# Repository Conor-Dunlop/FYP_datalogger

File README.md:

# ENEL400 datalogger

render of the datalogger with power board (yes i know it need routed)

this project has 2 main dirs
## hardware
this is where all the schmatics and PCBs live
within here you have the 
- `WB_based_board/datalogger` depecated one of lui projects that uses an stm32 with wireless built in
- `g4_based_board` has the schmatics and PCB for the datalogger
- `libs` for custom parts that wernt in kicad
- `lorawan_board/LoRaWAN_Board` never used dont look at this
- `power_board` as a power board that support 1 cell lipo and an external dc voltage
- `power_supply_module` i have forgotten more then likely the same as power_board

## software
this is where all the software for the project lives
- `conor code` this is where some depecated stm32cube projects live
- `ESP32_comms` this is where a basic code for the ESP32 lives
  - this code allow for any data spat out form the data logger to be sent off through an https request to some server, (i would suggest using the server in `emulator`)
- `Heltec ESP32 code` this is where the code live for a basic lorawan setup live 
- `joshM code/OLD_BOARD_SOFTWARE_UART_COMMS` this is josh Ms "Fork" of the `OLD_BOARD_SOFTWARE_UART_COMMS` code
- `New_G4_Software` this has basic code for the most recent PCB use the `NEW_G4_software.ioc` for creating any new projects you may need
- `OLD_BOARD_SOFTWARE_UART_COMMS` this is code that send a count a button count, a state that can be changed with buttons and an ADC value that gets sent over comms interface using UART, to be used in tandom with the `ESP32_comms` code
- `WB_software` depecated uses an stm32 that has wireless support
- `data_formats` holds the schema for the database on asure
- `dataloggerAPI` asure cloud server that handles all the HTTP requests and database lookups
- `emulator` emulates the datalogger so you can test server code with out a physical data logger 
- `g4_software` depecated fpr use on the original board

for any ESP32 code it is suggested to connect to a moblie hot spot as the uc wireless doesnt like them.
the software is a mess because some people dont know how to branch code

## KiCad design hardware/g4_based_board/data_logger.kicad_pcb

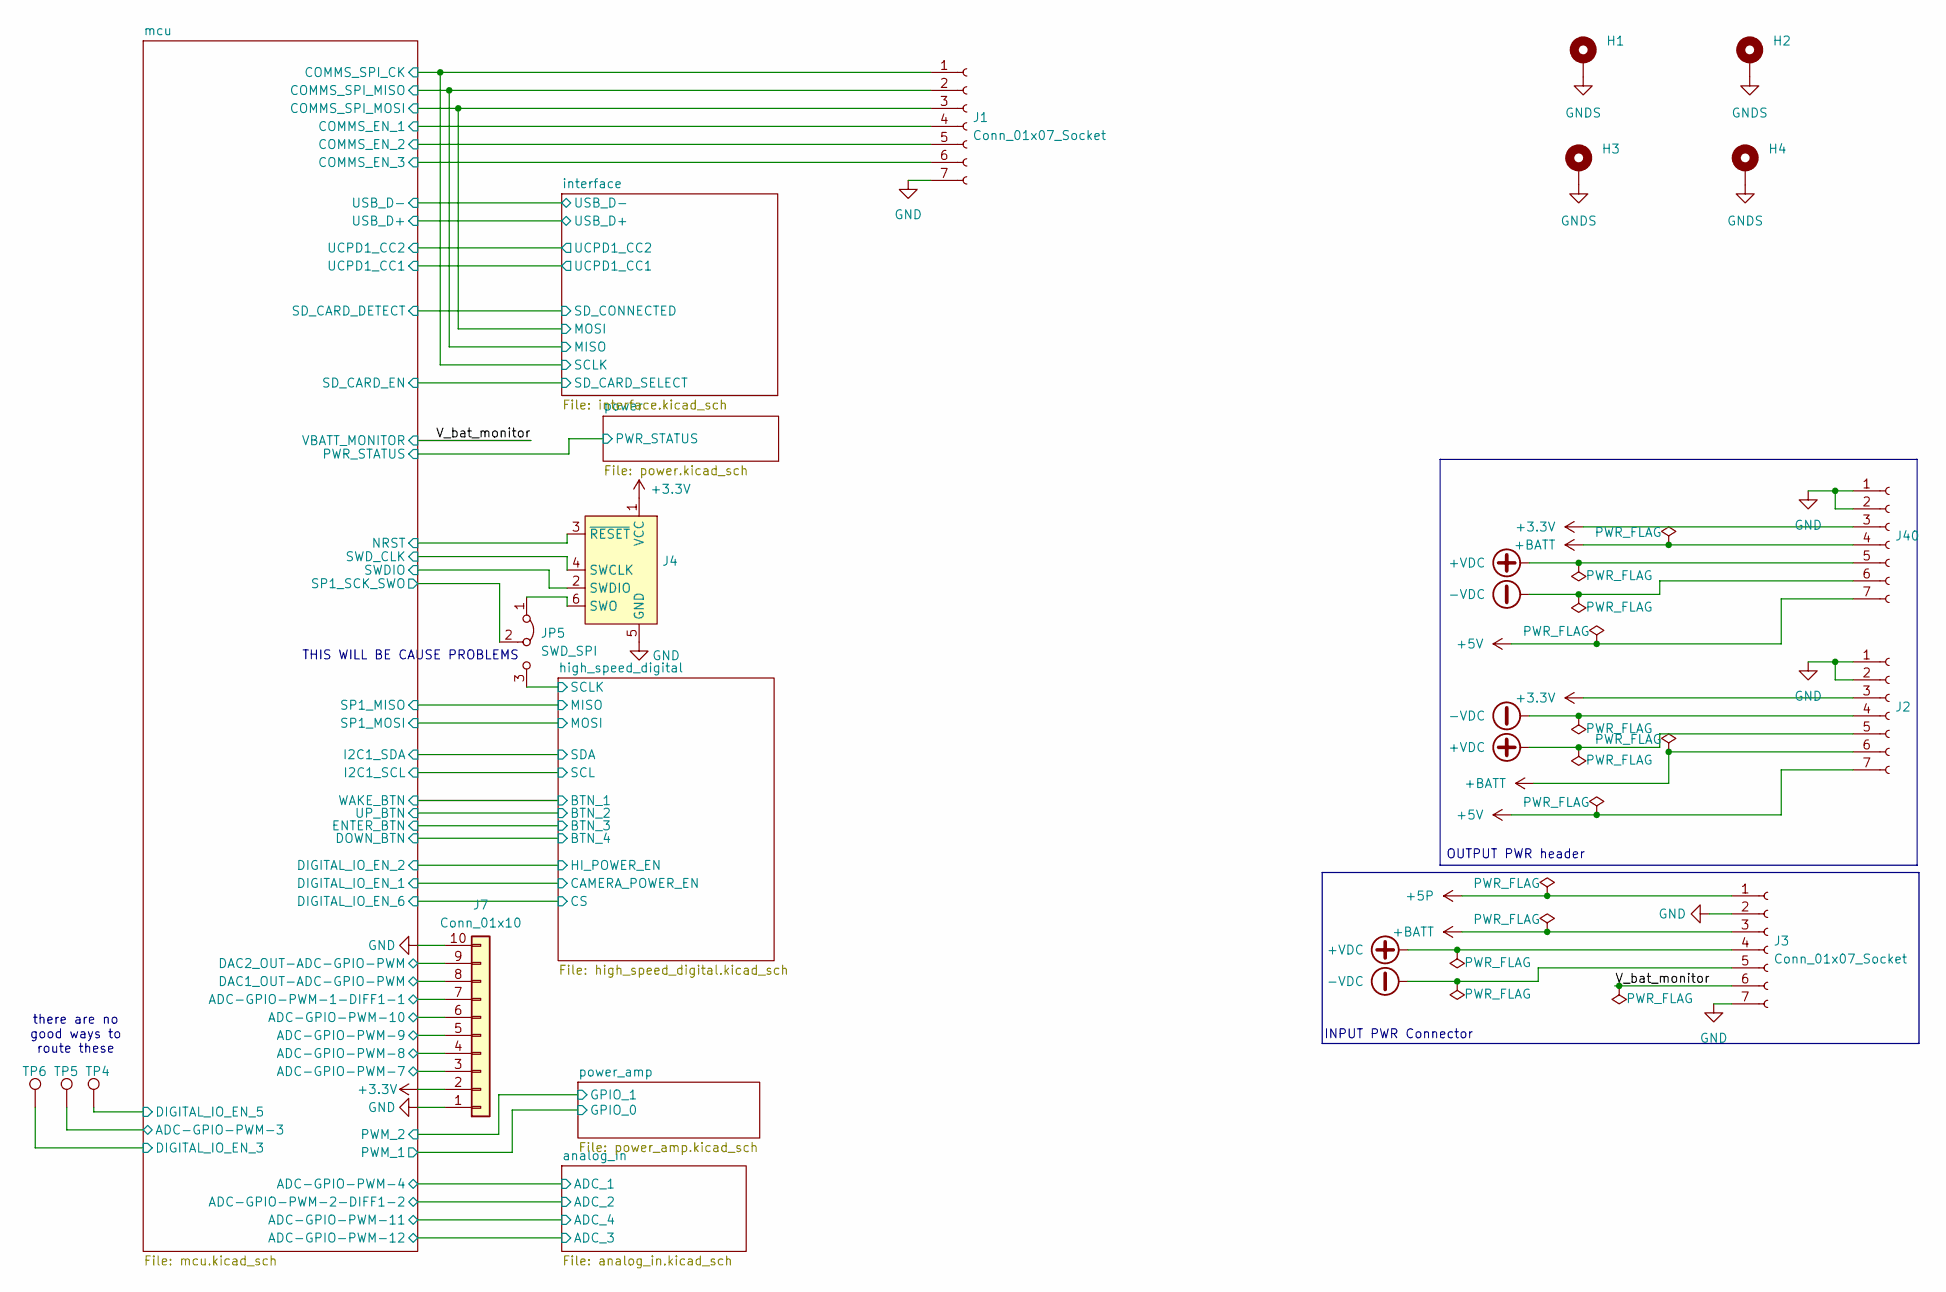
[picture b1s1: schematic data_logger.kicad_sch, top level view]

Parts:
H1, H2, H3, H4: MountingHole_Pad; MountingHole_3.2mm_M3_DIN965_Pad_TopOnly
J1, J2, J3, J40: Conn_01x07_Socket; PinHeader_1x07_P2.54mm_Vertical
J4: Conn_ARM_SWD_TagConnect_TC2030-NL; Tag-Connect_TC2030-IDC-FP_2x03_P1.27mm_Vertical
J7: Conn_01x10; PinHeader_1x10_P2.54mm_Vertical
JP5: SWD_SPI; SolderJumper-3_P1.3mm_Bridged2Bar12_RoundedPad1.0x1.5mm
TP4, TP5, TP6: TestPoint; TestPoint_Pad_2.0x2.0mm

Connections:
+3.3V: J2.3, J4.1 (VCC), J7.2, J40.3; also elsewhere on the board
+5P: J3.1; also elsewhere on the board
+5V: J2.7, J40.7; also elsewhere on the board
+BATT: J2.6, J3.3, J40.4; also elsewhere on the board
+VDC: J2.5, J3.4, J40.5
-VDC: J2.4, J3.5, J40.6
/V_bat_monitor: J3.6; also elsewhere on the board
/high_speed_digital/SCLK: JP5.3 (B); also elsewhere on the board
/interface/MISO: J1.2; also elsewhere on the board
/interface/MOSI: J1.3; also elsewhere on the board
/interface/SCLK: J1.1; also elsewhere on the board
/mcu/ADC-GPIO-PWM-1-DIFF1-1: J7.7; also elsewhere on the board
/mcu/ADC-GPIO-PWM-3: TP5.1; also elsewhere on the board
/mcu/ADC-GPIO-PWM-7: J7.3; also elsewhere on the board
/mcu/ADC-GPIO-PWM-8: J7.4; also elsewhere on the board
/mcu/ADC-GPIO-PWM-9: J7.5; also elsewhere on the board
/mcu/ADC-GPIO-PWM-10: J7.6; also elsewhere on the board
/mcu/COMMS_EN_1: J1.4; also elsewhere on the board
/mcu/COMMS_EN_2: J1.5; also elsewhere on the board
/mcu/COMMS_EN_3: J1.6; also elsewhere on the board
/mcu/DAC1_OUT-ADC-GPIO-PWM: J7.8; also elsewhere on the board
/mcu/DAC2_OUT-ADC-GPIO-PWM: J7.9; also elsewhere on the board
/mcu/DIGITAL_IO_EN_3: TP6.1; also elsewhere on the board
/mcu/DIGITAL_IO_EN_5: TP4.1; also elsewhere on the board
/mcu/NRST: J4.3 (~RESET); also elsewhere on the board
/mcu/SP1_SCK_SWO: JP5.2 (C); also elsewhere on the board
/mcu/SWDIO: J4.2 (SWDIO); also elsewhere on the board
/mcu/SWD_CLK: J4.4 (SWCLK); also elsewhere on the board
GND: J1.7, J2.1, J2.2, J3.2, J3.7, J4.5 (GND), J7.1, J7.10, J40.1, J40.2; also elsewhere on the board
GNDS: H1.1, H2.1, H3.1, H4.1; also elsewhere on the board
unnamed: J4.6 (SWO), JP5.1 (A)

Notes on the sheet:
THIS WILL BE CAUSE PROBLEMS
INPUT PWR Connector
there are no good ways to route these
OUTPUT PWR header

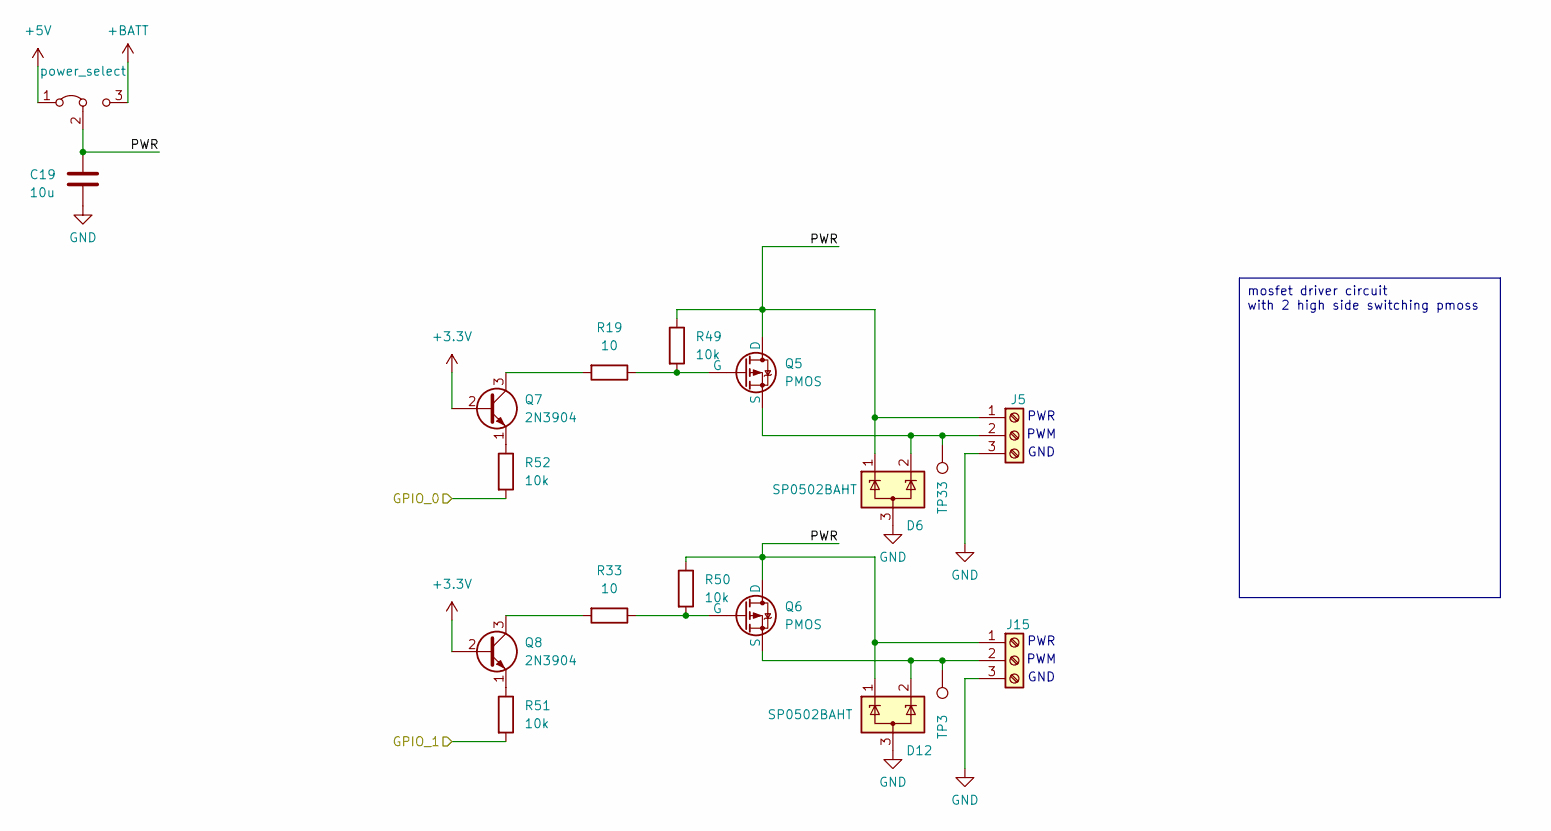
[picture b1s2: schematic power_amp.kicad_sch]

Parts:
C19: 10u; C_0603_1608Metric_Pad1.08x0.95mm_HandSolder
D6, D12: SP0502BAHT; SOT-23
J5, J15: Screw_Terminal_01x03; TerminalBlock_Altech_AK300-3_P5.00mm
JP6: power_select; PinHeader_1x03_P2.54mm_Vertical
Q5, Q6: PMOS; TO-247-3_Vertical
Q7, Q8: 2N3904; TO-92_Inline
R19, R33: 10; R_0603_1608Metric_Pad0.98x0.95mm_HandSolder
R49, R50, R51, R52: 10k; R_0603_1608Metric_Pad0.98x0.95mm_HandSolder
TP3, TP33: GPIO_INPUT_PRE; TestPoint_Keystone_5019_Minature

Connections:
+3.3V: Q7.2 (B), Q8.2 (B); also elsewhere on the board
+5V: JP6.1 (A); also elsewhere on the board
+BATT: JP6.3 (B); also elsewhere on the board
/mcu/PWM_1: R52.2; also elsewhere on the board
/mcu/PWM_2: R51.2; also elsewhere on the board
/power_amp/PWR: C19.1, D6.1 (K), D12.1 (K), J5.1, J15.1, JP6.2 (C), Q5.1 (D), Q6.1 (D), R49.1, R50.1
GND: C19.2, D6.3 (A), D12.3 (A), J5.3, J15.3; also elsewhere on the board
unnamed: D6.2 (K), J5.2, Q5.3 (S), TP33.1
unnamed: D12.2 (K), J15.2, Q6.3 (S), TP3.1
unnamed: Q5.2 (G), R19.1, R49.2
unnamed: Q6.2 (G), R33.1, R50.2
unnamed: Q7.3 (C), R19.2
unnamed: Q7.1 (E), R52.1
unnamed: Q8.3 (C), R33.2
unnamed: Q8.1 (E), R51.1

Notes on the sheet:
mosfet driver circuit with 2 high side switching pmoss
GND
PWR
PWM

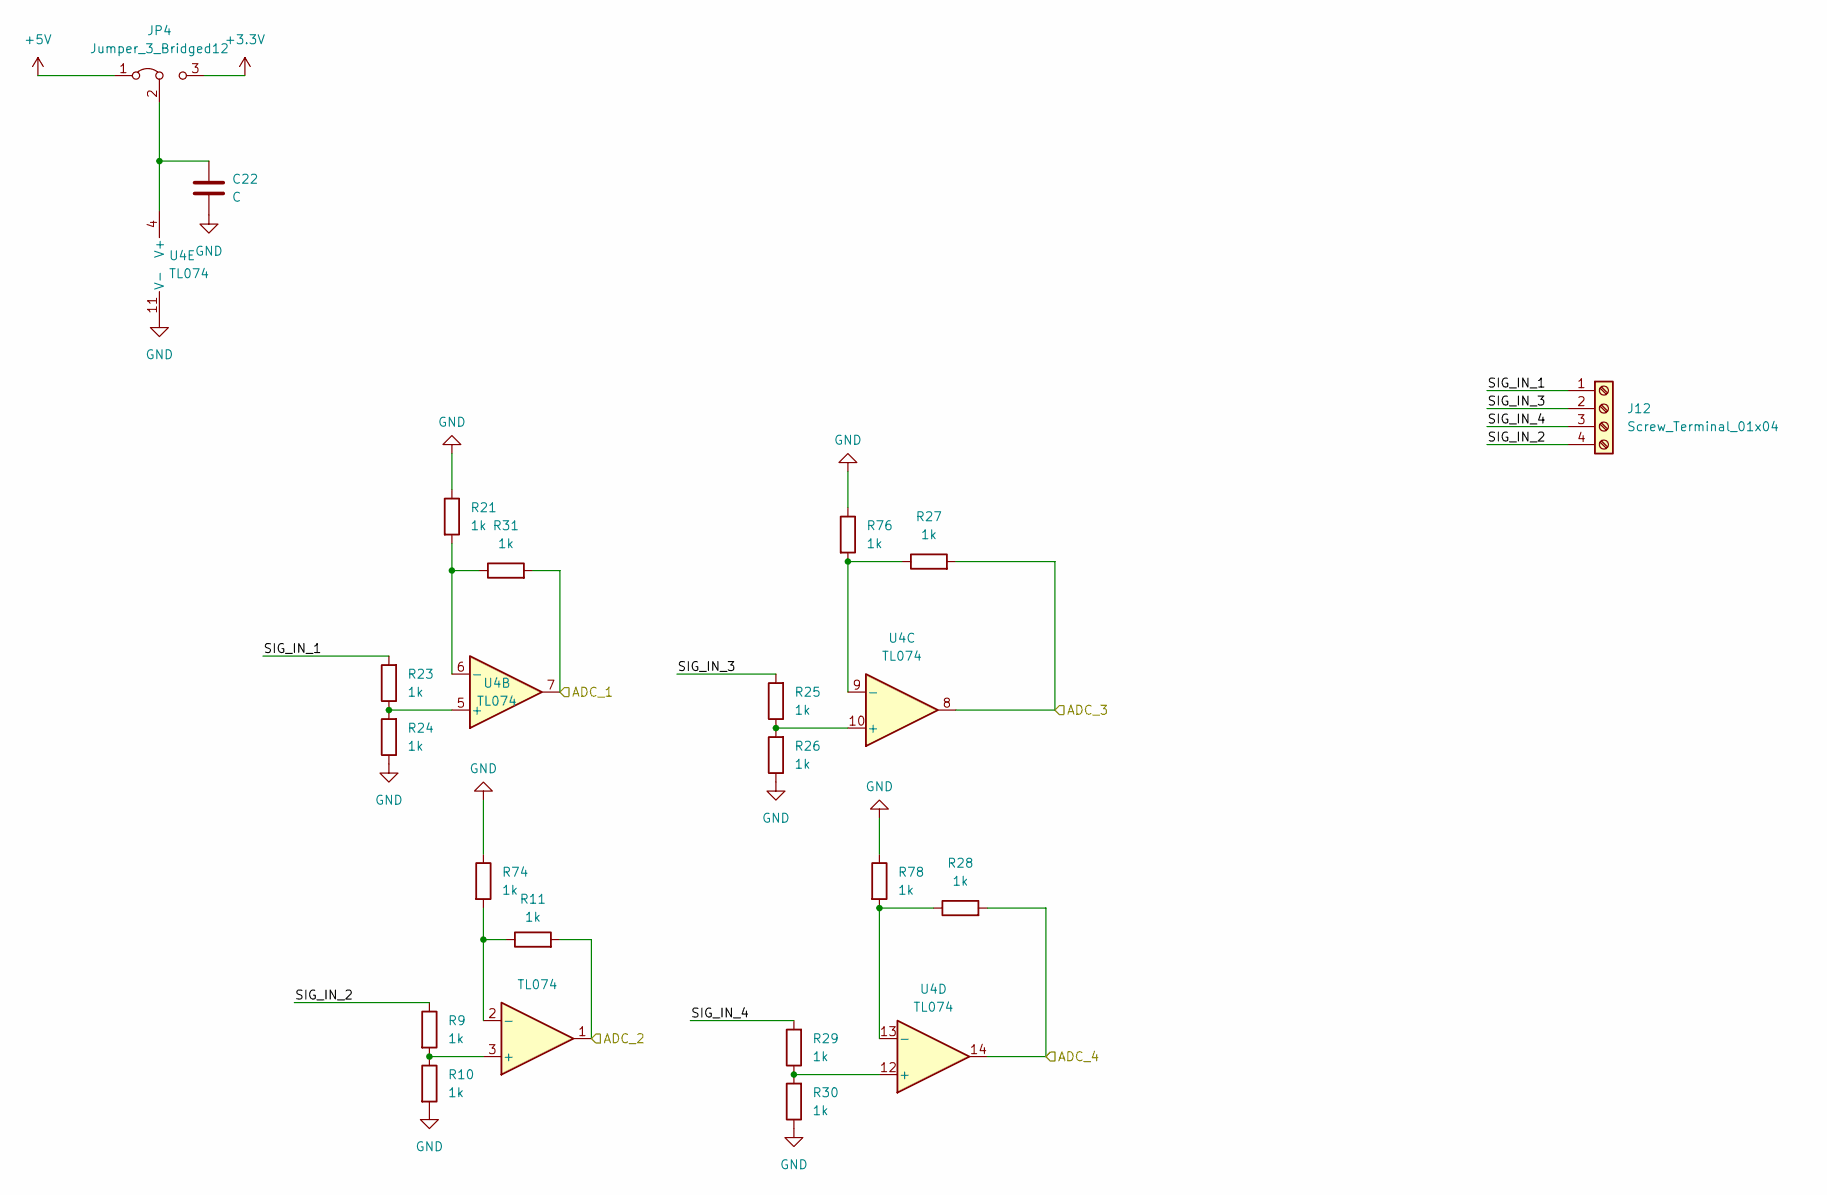
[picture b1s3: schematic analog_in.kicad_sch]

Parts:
C22: C; C_0603_1608Metric_Pad1.08x0.95mm_HandSolder
J12: Screw_Terminal_01x04; TerminalBlock_Altech_AK300-4_P5.00mm
JP4: Jumper_3_Bridged12; PinHeader_1x03_P2.54mm_Vertical
R9, R10, R11, R21, R23, R24, R25, R26, R27, R28, R29, R30, R31, R74, R76, R78: 1k; R_0603_1608Metric_Pad0.98x0.95mm_HandSolder
U4: TL074; SOIC-14_3.9x8.7mm_P1.27mm

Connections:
+3.3V: JP4.3 (B); also elsewhere on the board
+5V: JP4.1 (A); also elsewhere on the board
/analog_in/ADC_1: R31.2, U4.7; also elsewhere on the board
/analog_in/ADC_2: R11.2, U4.1; also elsewhere on the board
/analog_in/ADC_3: R27.2, U4.8; also elsewhere on the board
/analog_in/ADC_4: R28.2, U4.14; also elsewhere on the board
/analog_in/SIG_IN_2: J12.4, R9.1
/analog_in/SIG_IN_3: J12.2, R25.2
GND: C22.2, R10.2, R21.1, R24.1, R26.1, R30.1, R74.1, R76.1, R78.1, U4.11 (V-); also elsewhere on the board
unnamed: C22.1, JP4.2 (C), U4.4 (V+)
unnamed: R9.2, R10.1, U4.3 (+)
unnamed: R11.1, R74.2, U4.2 (-)
unnamed: R23.1, R24.2, U4.5 (+)
unnamed: R21.2, R31.1, U4.6 (-)
unnamed: R25.1, R26.2, U4.10 (+)
unnamed: R27.1, R76.2, U4.9 (-)
unnamed: R29.1, R30.2, U4.12 (+)
unnamed: R28.1, R78.2, U4.13 (-)

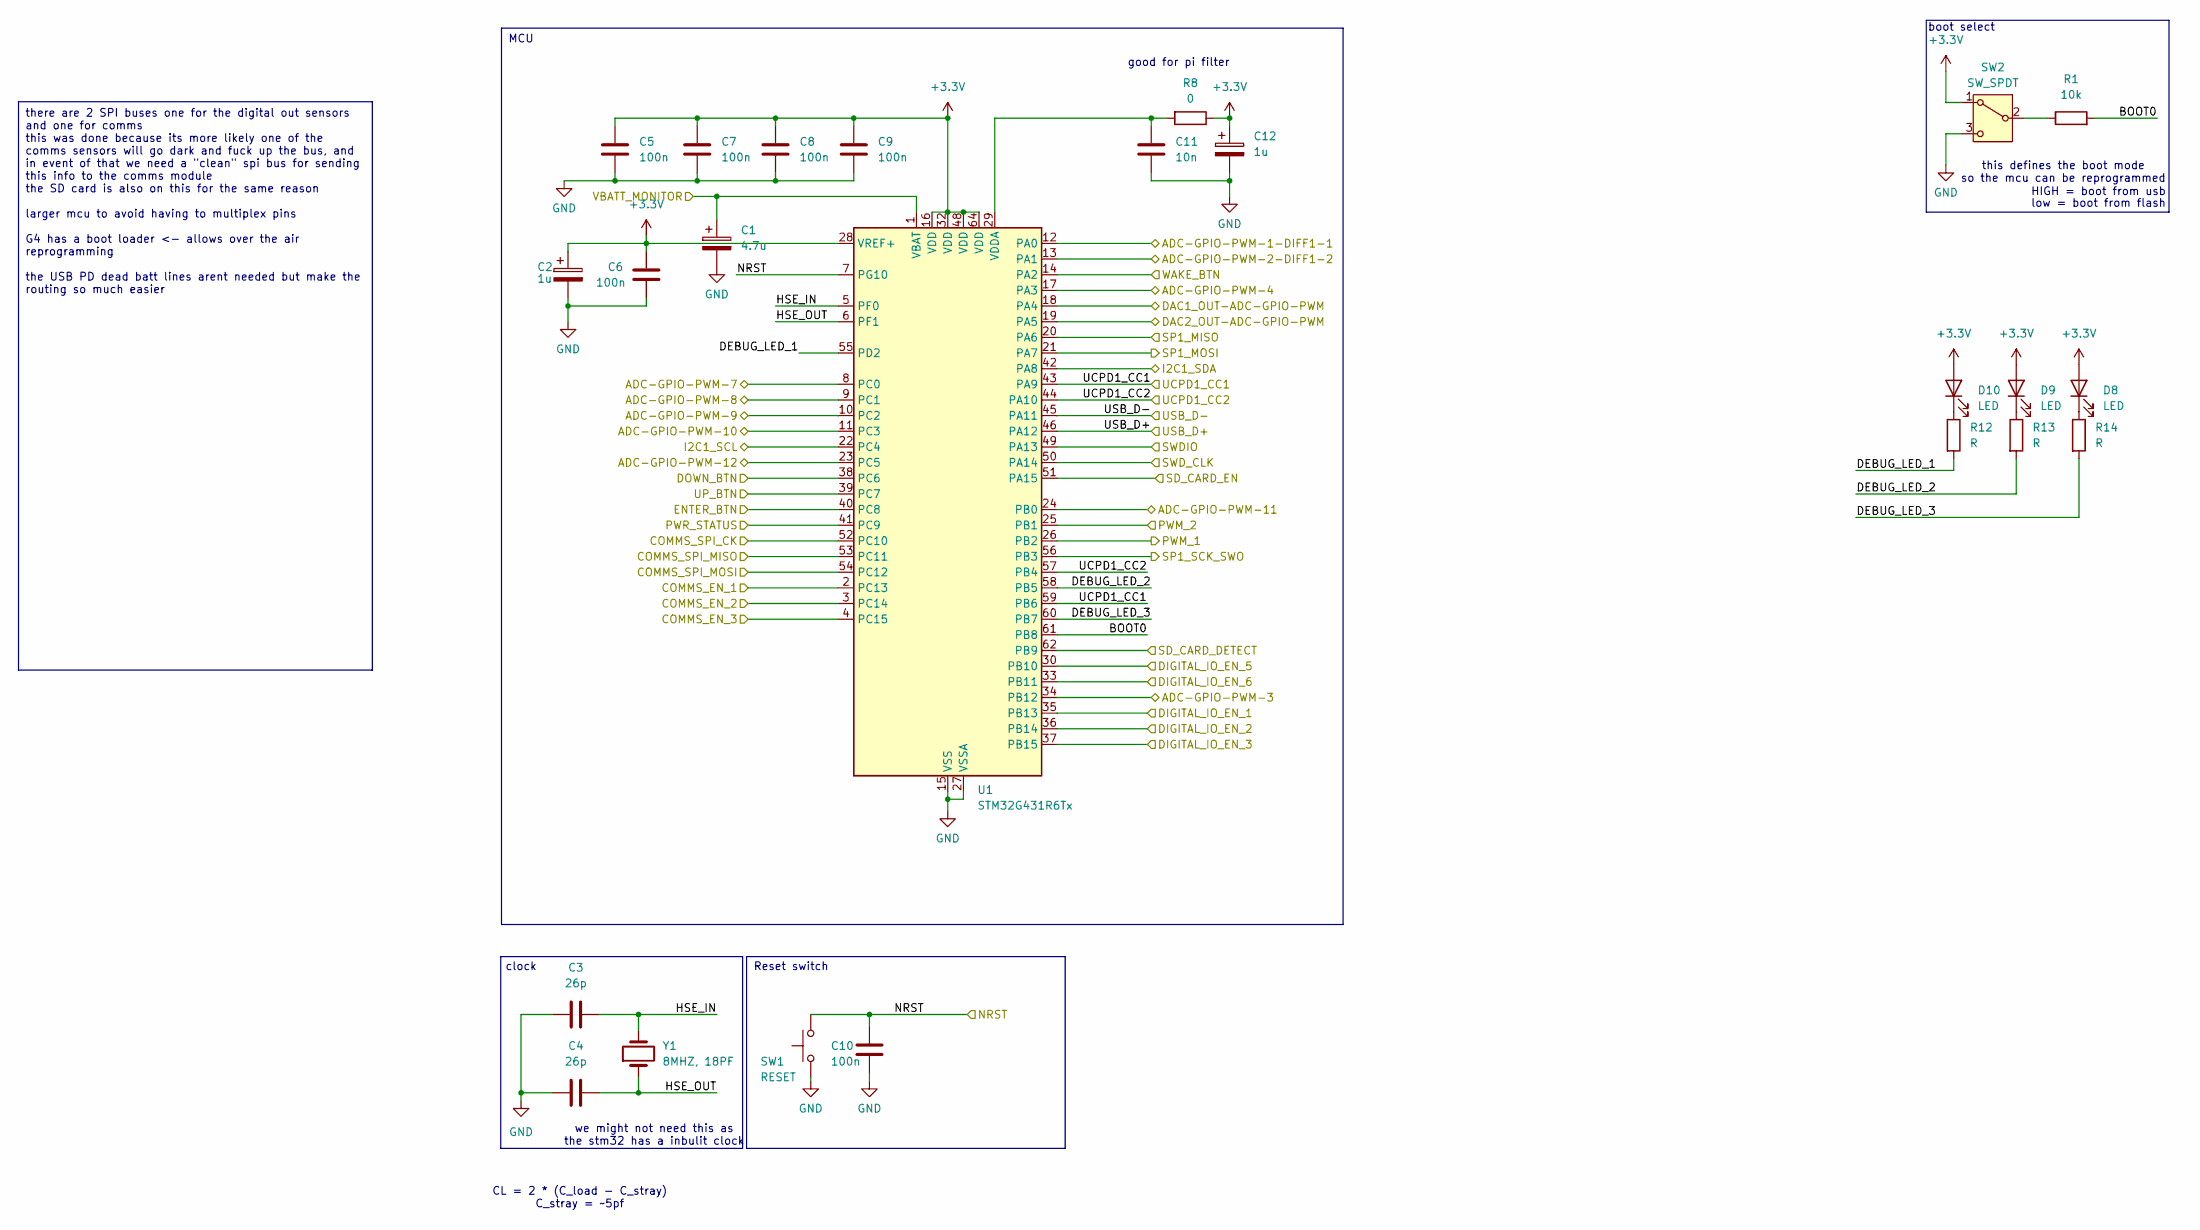
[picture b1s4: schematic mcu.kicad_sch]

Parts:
C1: 4.7u; C_0603_1608Metric_Pad1.08x0.95mm_HandSolder
C2, C12: 1u; C_0603_1608Metric_Pad1.08x0.95mm_HandSolder
C3, C4: 26p; C_0603_1608Metric_Pad1.08x0.95mm_HandSolder
C5, C6, C7, C8, C9, C10: 100n; C_0603_1608Metric_Pad1.08x0.95mm_HandSolder
C11: 10n; C_0603_1608Metric_Pad1.08x0.95mm_HandSolder
D8, D9, D10: LED; LED_0603_1608Metric
R1: 10k; R_0603_1608Metric_Pad0.98x0.95mm_HandSolder
R8: 0; R_0603_1608Metric
R12, R13, R14: R; R_0603_1608Metric_Pad0.98x0.95mm_HandSolder
SW1: RESET; SW_Push_SPST_NO_Alps_SKRK
SW2: SW_SPDT; SW_Slide_SPDT_Angled_CK_OS102011MA1Q
U1: STM32G431R6Tx; LQFP-64_10x10mm_P0.5mm
Y1: 8MHZ, 18PF; Crystal_SMD_TXC_7A-2Pin_5x3.2mm

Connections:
+3.3V: C2.1, C5.1, C6.1, C7.1, C8.1, C9.1, C12.1, D8.2 (A), D9.2 (A), D10.2 (A), R8.1, SW2.1 (A), U1.16 (VDD), U1.28 (VREF+), U1.32 (VDD), U1.48 (VDD), U1.64 (VDD); also elsewhere on the board
/V_bat_monitor: C1.1, U1.1 (VBAT); also elsewhere on the board
/analog_in/ADC_1: U1.17 (PA3); also elsewhere on the board
/analog_in/ADC_2: U1.13 (PA1); also elsewhere on the board
/analog_in/ADC_3: U1.23 (PC5); also elsewhere on the board
/analog_in/ADC_4: U1.24 (PB0); also elsewhere on the board
/high_speed_digital/BTN_1: U1.14 (PA2); also elsewhere on the board
/high_speed_digital/BTN_2: U1.39 (PC7); also elsewhere on the board
/high_speed_digital/BTN_3: U1.40 (PC8); also elsewhere on the board
/high_speed_digital/BTN_4: U1.38 (PC6); also elsewhere on the board
/high_speed_digital/CAMERA_POWER_EN: U1.35 (PB13); also elsewhere on the board
/high_speed_digital/CS: U1.33 (PB11); also elsewhere on the board
/high_speed_digital/HI_POWER_EN: U1.36 (PB14); also elsewhere on the board
/high_speed_digital/MISO: U1.20 (PA6); also elsewhere on the board
/high_speed_digital/MOSI: U1.21 (PA7); also elsewhere on the board
/interface/MISO: U1.53 (PC11); also elsewhere on the board
/interface/MOSI: U1.54 (PC12); also elsewhere on the board
/interface/SCLK: U1.52 (PC10); also elsewhere on the board
/interface/SD_CARD_SELECT: U1.51 (PA15); also elsewhere on the board
/interface/SD_CONNECTED: U1.62 (PB9); also elsewhere on the board
/mcu/ADC-GPIO-PWM-1-DIFF1-1: U1.12 (PA0); also elsewhere on the board
/mcu/ADC-GPIO-PWM-3: U1.34 (PB12); also elsewhere on the board
/mcu/ADC-GPIO-PWM-7: U1.8 (PC0); also elsewhere on the board
/mcu/ADC-GPIO-PWM-8: U1.9 (PC1); also elsewhere on the board
/mcu/ADC-GPIO-PWM-9: U1.10 (PC2); also elsewhere on the board
/mcu/ADC-GPIO-PWM-10: U1.11 (PC3); also elsewhere on the board
/mcu/BOOT0: R1.2, U1.61 (PB8)
/mcu/COMMS_EN_1: U1.2 (PC13); also elsewhere on the board
/mcu/COMMS_EN_2: U1.3 (PC14); also elsewhere on the board
/mcu/COMMS_EN_3: U1.4 (PC15); also elsewhere on the board
/mcu/DAC1_OUT-ADC-GPIO-PWM: U1.18 (PA4); also elsewhere on the board
/mcu/DAC2_OUT-ADC-GPIO-PWM: U1.19 (PA5); also elsewhere on the board
/mcu/DEBUG_LED_1: R12.2, U1.55 (PD2)
/mcu/DEBUG_LED_2: R13.2, U1.58 (PB5)
/mcu/DEBUG_LED_3: R14.2, U1.60 (PB7)
/mcu/DIGITAL_IO_EN_3: U1.37 (PB15); also elsewhere on the board
/mcu/DIGITAL_IO_EN_5: U1.30 (PB10); also elsewhere on the board
/mcu/HSE_IN: C3.1, U1.5 (PF0), Y1.2
/mcu/HSE_OUT: C4.1, U1.6 (PF1), Y1.1
/mcu/NRST: C10.2, SW1.2, U1.7 (PG10); also elsewhere on the board
/mcu/PWM_1: U1.26 (PB2); also elsewhere on the board
/mcu/PWM_2: U1.25 (PB1); also elsewhere on the board
/mcu/PWR_STATUS: U1.41 (PC9); also elsewhere on the board
/mcu/SP1_SCK_SWO: U1.56 (PB3); also elsewhere on the board
/mcu/SWDIO: U1.49 (PA13); also elsewhere on the board
/mcu/SWD_CLK: U1.50 (PA14); also elsewhere on the board
/mcu/UCPD1_CC1: U1.43 (PA9), U1.59 (PB6); also elsewhere on the board
/mcu/UCPD1_CC2: U1.44 (PA10), U1.57 (PB4); also elsewhere on the board
/mcu/USB_D+: U1.46 (PA12); also elsewhere on the board
/mcu/USB_D-: U1.45 (PA11); also elsewhere on the board
GND: C1.2, C2.2, C3.2, C4.2, C5.2, C6.2, C7.2, C8.2, C9.2, C10.1, C11.2, C12.2, SW1.1, SW2.3 (C), U1.15 (VSS), U1.27 (VSSA), U1.31 (VSS), U1.47 (VSS), U1.63 (VSS); also elsewhere on the board
unnamed: D8.1 (K), R14.1
unnamed: D9.1 (K), R13.1
unnamed: D10.1 (K), R12.1
unnamed: R1.1, SW2.2 (B)
unnamed: C11.1, R8.2, U1.29 (VDDA)

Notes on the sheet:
there are 2 SPI buses one for the digital out sensors and one for comms this was done because its more likely one of the comms sensors will go dark and fuck up the bus, and in event of that we need a "clean" spi bus for sending this info to the comms module the SD card is also on this for the same 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
good for pi filter
boot select
clock
MCU
Reset switch
HIGH = boot from usb
CL = 2 * (C_load - C_stray) C_stray = ~5pf
this defines the boot mode so the mcu can be reprogrammed
low = boot from flash
we might not need this as the stm32 has a inbulit clock

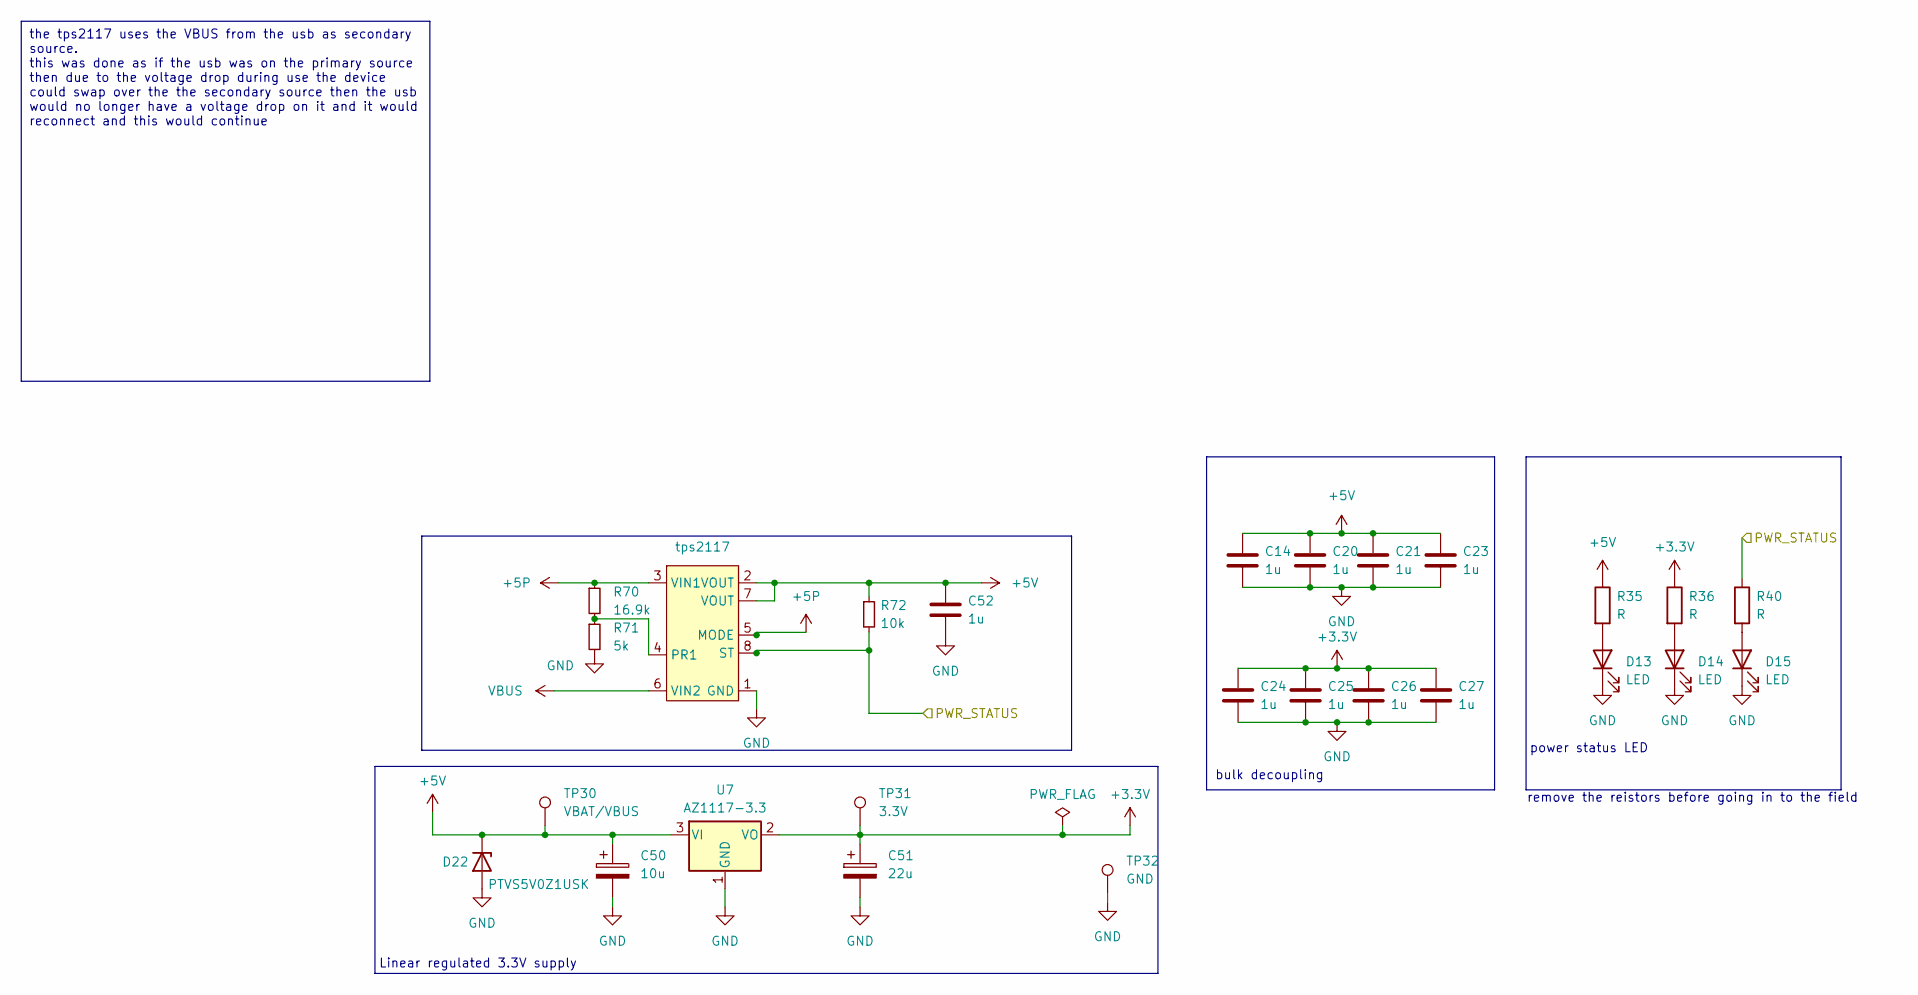
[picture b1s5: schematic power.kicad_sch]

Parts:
C14, C20, C21, C23, C24, C25, C26, C27, C52: 1u; C_0603_1608Metric_Pad1.08x0.95mm_HandSolder
C50: 10u; C_0603_1608Metric_Pad1.08x0.95mm_HandSolder
C51: 22u; C_0603_1608Metric_Pad1.08x0.95mm_HandSolder
D13, D14, D15: LED; LED_0603_1608Metric
D22: PTVS5V0Z1USK; Nexperia_DSN1608-2_1.6x0.8mm
R35, R36, R40: R; R_0603_1608Metric_Pad0.98x0.95mm_HandSolder
R70: 16.9k; R_0603_1608Metric_Pad0.98x0.95mm_HandSolder
R71: 5k; R_0603_1608Metric_Pad0.98x0.95mm_HandSolder
R72: 10k; R_0603_1608Metric_Pad0.98x0.95mm_HandSolder
TP30: VBAT/VBUS; TestPoint_Pad_D1.5mm
TP31: 3.3V; TestPoint_Pad_D1.5mm
TP32: GND; TestPoint_Pad_D1.5mm
U6: tps2117; SOT-583-8
U7: AZ1117-3.3; SOT-223

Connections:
+3.3V: C24.1, C25.1, C26.1, C27.1, C51.1, R36.1, TP31.1, U7.2 (VO); also elsewhere on the board
+5P: R70.1, U6.3 (VIN1), U6.5 (MODE); also elsewhere on the board
+5V: C14.1, C20.1, C21.1, C23.1, C50.1, C52.1, D22.1 (K), R35.1, R72.1, TP30.1, U6.2 (VOUT), U6.7 (VOUT), U7.3 (VI); also elsewhere on the board
/mcu/PWR_STATUS: R40.1, R72.2, U6.8 (ST); also elsewhere on the board
GND: C14.2, C20.2, C21.2, C23.2, C24.2, C25.2, C26.2, C27.2, C50.2, C51.2, C52.2, D13.1 (K), D14.1 (K), D15.1 (K), D22.2 (A), R71.2, TP32.1, U6.1 (GND), U7.1 (GND); also elsewhere on the board
unnamed: D13.2 (A), R35.2
unnamed: D14.2 (A), R36.2
unnamed: D15.2 (A), R40.2
unnamed: R70.2, R71.1, U6.4 (PR1)
VBUS: U6.6 (VIN2); also elsewhere on the board

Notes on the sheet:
the tps2117 uses the VBUS from the usb as secondary source. this was done as if the usb was on the primary source then due to the voltage drop during use the device could swap over the the secondary source then the usb would no longer have a voltage drop on it and it would reconnect and this would 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
bulk decoupling
remove the reistors before going in to the field
Linear regulated 3.3V supply
power status LED

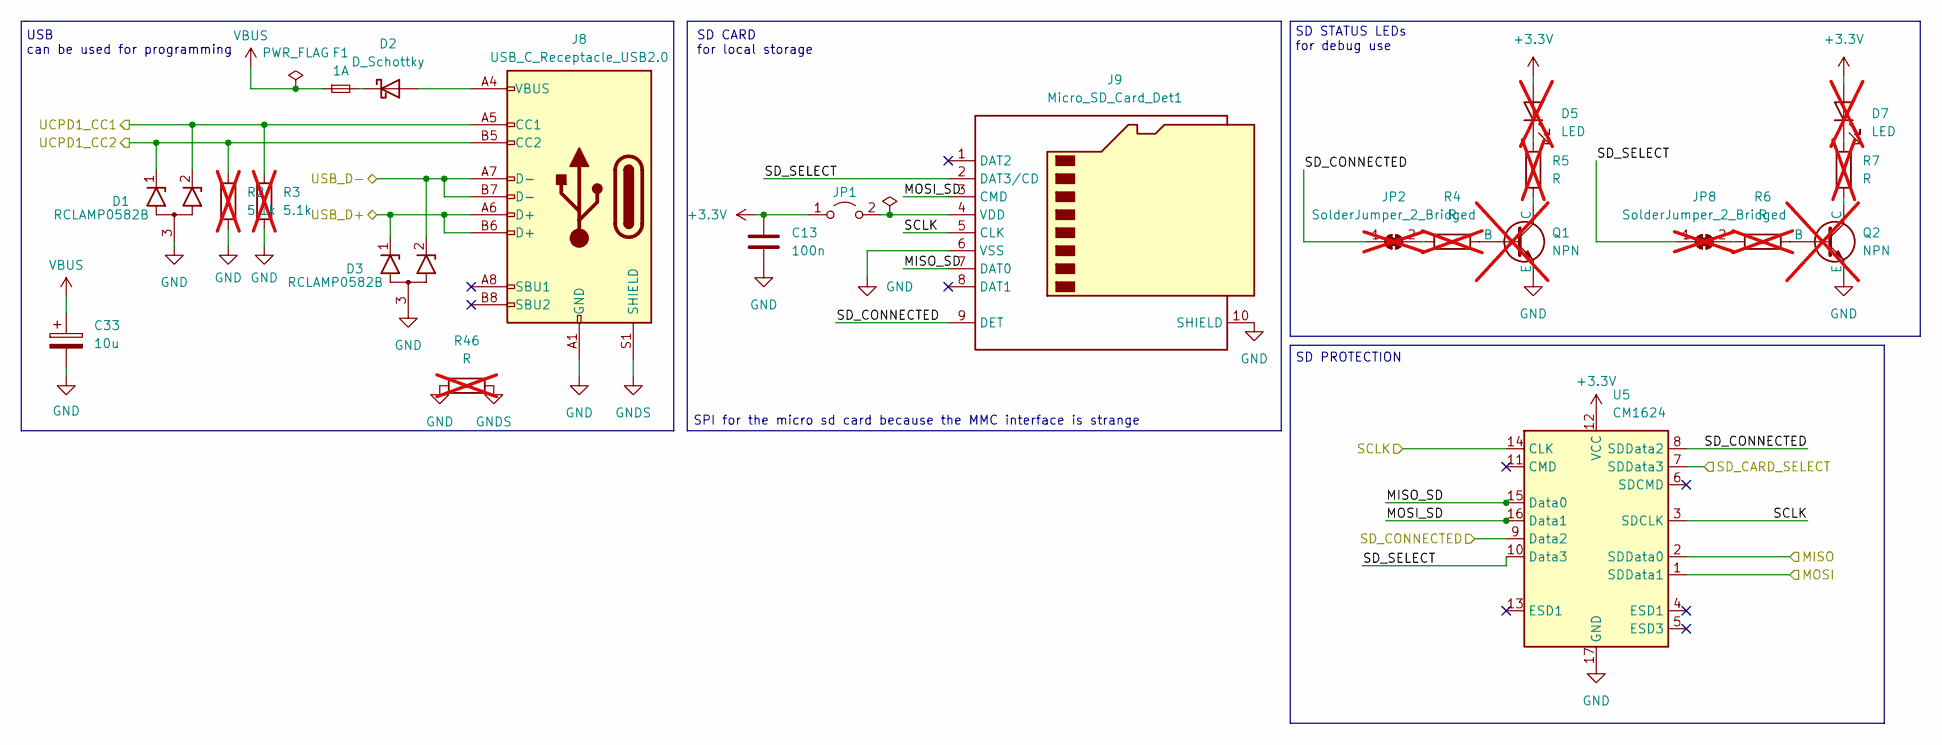
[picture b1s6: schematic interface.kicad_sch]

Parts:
C13: 100n; C_0603_1608Metric_Pad1.08x0.95mm_HandSolder
C33: 10u; C_0603_1608Metric_Pad1.08x0.95mm_HandSolder
D1, D3: RCLAMP0582B; SOT-416
D2: D_Schottky; D_0805_2012Metric_Pad1.15x1.40mm_HandSolder
D5, D7: LED; LED_0603_1608Metric; not fitted
F1: 1A; Fuse_0805_2012Metric_Pad1.15x1.40mm_HandSolder
J8: USB_C_Receptacle_USB2.0; USB_C_Receptacle_HRO_TYPE-C-31-M-12
J9: Micro_SD_Card_Det1; microSD_HC_Hirose_DM3BT-DSF-PEJS
JP1: Jumper_2_Open; SolderJumper-2_P1.3mm_Open_TrianglePad1.0x1.5mm
JP2, JP8: SolderJumper_2_Bridged; SolderJumper-2_P1.3mm_Bridged_Pad1.0x1.5mm; not fitted
Q1, Q2: NPN; TSOT-23; not fitted
R2, R3: 5.1k; R_0603_1608Metric_Pad0.98x0.95mm_HandSolder; not fitted
R4, R5, R6, R7, R46: R; R_0603_1608Metric_Pad0.98x0.95mm_HandSolder; not fitted
U5: CM1624; OnSemi_UDFN-16-1EP_1.35x3.3mm_P0.4mm_EP0.4x2.8mm

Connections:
+3.3V: C13.1, D5.2 (A), D7.2 (A), JP1.1 (A), U5.12 (VCC); also elsewhere on the board
/interface/MISO: U5.2 (SDData0); also elsewhere on the board
/interface/MISO_SD: J9.7 (DAT0), U5.15 (Data0)
/interface/MOSI: U5.1 (SDData1); also elsewhere on the board
/interface/MOSI_SD: J9.3 (CMD), U5.16 (Data1)
/interface/SCLK: J9.5 (CLK), U5.3 (SDCLK), U5.14 (CLK); also elsewhere on the board
/interface/SD_CARD_SELECT: U5.7 (SDData3); also elsewhere on the board
/interface/SD_CONNECTED: J9.9 (DET), JP2.1 (A), U5.8 (SDData2), U5.9 (Data2); also elsewhere on the board
/interface/SD_SELECT: J9.2 (DAT3/CD), JP8.1 (A), U5.10 (Data3)
/mcu/UCPD1_CC1: D1.2 (K2), J8.A5 (CC1), R3.1; also elsewhere on the board
/mcu/UCPD1_CC2: D1.1 (K1), J8.B5 (CC2), R2.1; also elsewhere on the board
/mcu/USB_D+: D3.1 (K1), J8.A6 (D+), J8.B6 (D+); also elsewhere on the board
/mcu/USB_D-: D3.2 (K2), J8.A7 (D-), J8.B7 (D-); also elsewhere on the board
GND: C13.2, C33.2, D1.3 (A), D3.3 (A), J8.A1 (GND), J8.A12 (GND), J8.B1 (GND), J8.B12 (GND), J9.6 (VSS), J9.10 (SHIELD), Q1.3 (E), Q2.3 (E), R2.2, R3.2, R46.1, U5.17 (GND); also elsewhere on the board
GNDS: J8.S1 (SHIELD), R46.2; also elsewhere on the board
unnamed: D2.2 (A), J8.A4 (VBUS), J8.A9 (VBUS), J8.B4 (VBUS), J8.B9 (VBUS)
unnamed: D2.1 (K), F1.2
unnamed: D5.1 (K), R5.1
unnamed: D7.1 (K), R7.1
unnamed: J9.4 (VDD), JP1.2 (B)
unnamed: JP2.2 (B), R4.1
unnamed: JP8.2 (B), R6.1
unnamed: Q1.2 (B), R4.2
unnamed: Q1.1 (C), R5.2
unnamed: Q2.2 (B), R6.2
unnamed: Q2.1 (C), R7.2
VBUS: C33.1, F1.1; also elsewhere on the board

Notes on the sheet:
SD CARD for local storage
SD PROTECTION
USB can be used for programming
SD STATUS LEDs for debug use
SPI for the micro sd card because the MMC interface is strange
